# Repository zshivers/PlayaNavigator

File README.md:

# Install dependencies
- `brew install npm websocat`
- `cd test/interactive_map; npm install`
- `cd generated; npm install`

# Running Interactive Map Test
1. Compile for `host` target.
2. `npm start` - Starts the webserver with the map.
3. Go to http://localhost:5173
4. Run the host version, and pipe the websocket data into it - `websocat -s 9998 | ./.pio/build/host/program`

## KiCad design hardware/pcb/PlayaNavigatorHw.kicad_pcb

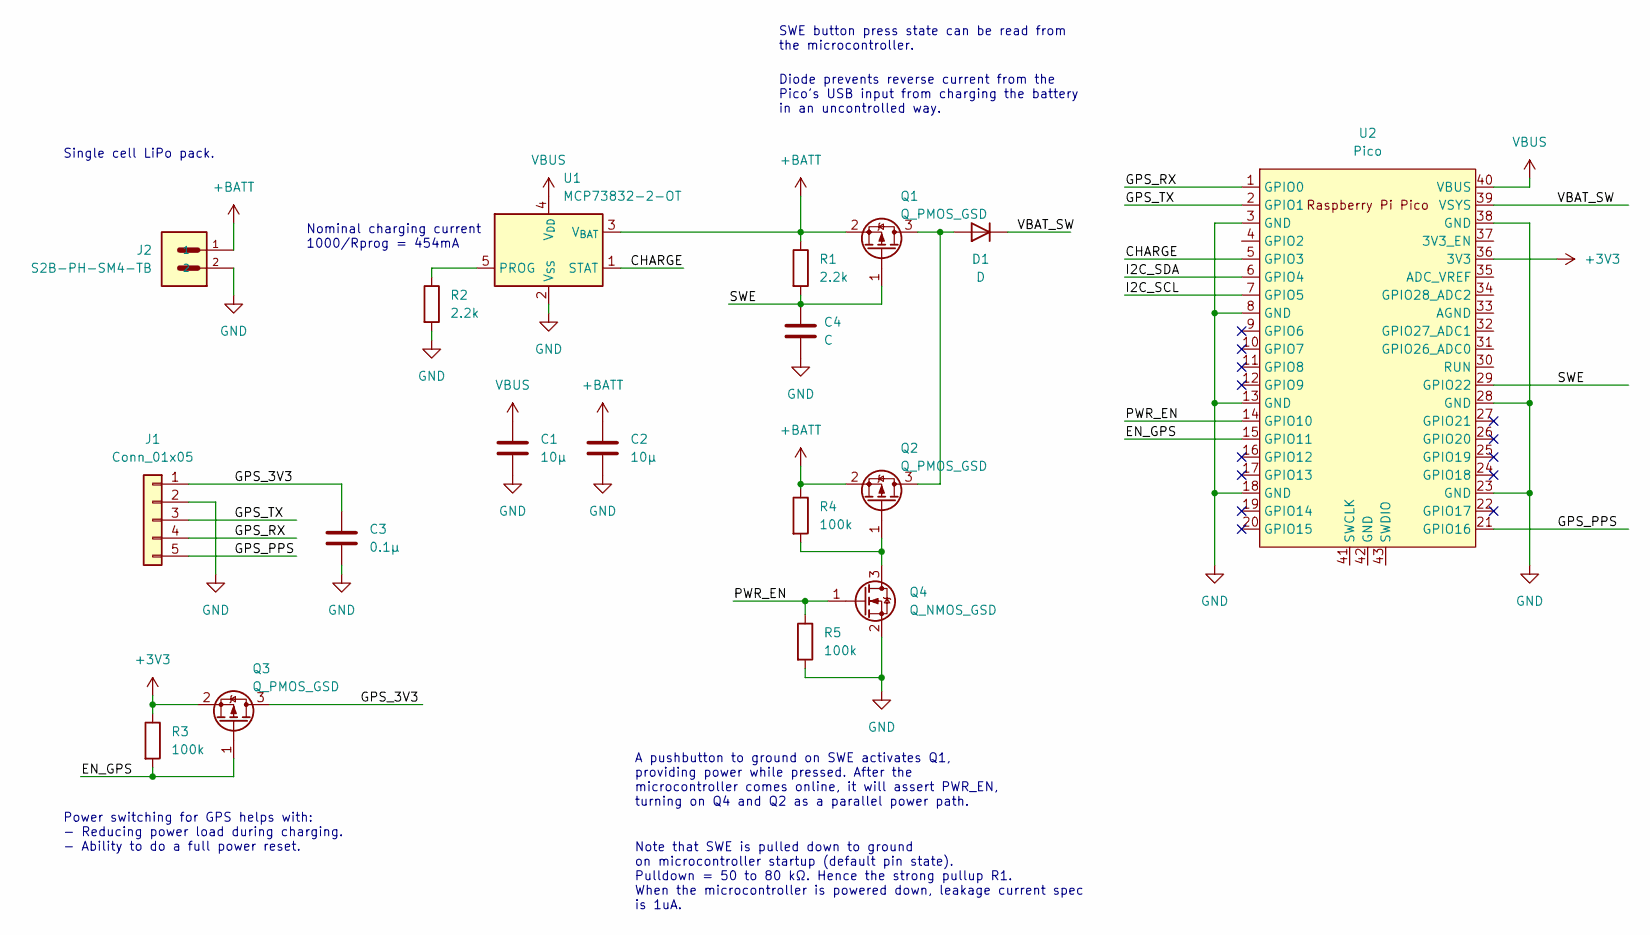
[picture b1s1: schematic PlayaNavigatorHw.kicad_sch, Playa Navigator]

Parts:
C1, C2: 10µ; C_1206_3216Metric
C3: 0.1µ; C_0805_2012Metric
C4: C; C_0805_2012Metric
D1: D; Nexperia_CFP3_SOD-123W
J1: Conn_01x05; PinHeader_1x05_P2.54mm_Vertical
J2: S2B-PH-SM4-TB; JST_S2B-PH-SM4-TB
Q1, Q2, Q3: Q_PMOS_GSD; SOT-23-3
Q4: Q_NMOS_GSD; SOT-23-3
R1, R2: 2.2k; C_0603_1608Metric
R3, R4, R5: 100k; C_0603_1608Metric
U1: MCP73832-2-OT; SOT-23-5; Digikey Part Number MCP73832-2ACI/MC-ND
U2: Pico; RPi_Pico_SMD_TH_Customized

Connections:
+3V3: Q3.2 (S), R3.1, U2.36 (3V3)
+BATT: C2.1, J2.1, Q1.2 (S), Q2.2 (S), R1.1, R4.1, U1.3 (V_{BAT})
/CHARGE: U1.1 (STAT), U2.5 (GPIO3)
/EN_GPS: Q3.1 (G), R3.2, U2.15 (GPIO11)
/GPS_3V3: C3.1, J1.1, Q3.3 (D)
/GPS_PPS: J1.5, U2.21 (GPIO16)
/GPS_RX: J1.4, U2.1 (GPIO0)
/GPS_TX: J1.3, U2.2 (GPIO1)
/I2C_SCL: U2.7 (GPIO5)
/I2C_SDA: U2.6 (GPIO4)
/PWR_EN: Q4.1 (G), R5.1, U2.14 (GPIO10)
/SWE: C4.1, Q1.1 (G), R1.2, U2.29 (GPIO22)
/VBAT_SW: D1.1 (K), U2.39 (VSYS)
GND: C1.2, C2.2, C3.2, C4.2, J1.2, J2.2, Q4.2 (S), R2.2, R5.2, U1.2 (V_{SS}), U2.3 (GND), U2.8 (GND), U2.13 (GND), U2.18 (GND), U2.23 (GND), U2.28 (GND), U2.38 (GND)
unnamed: D1.2 (A), Q1.3 (D), Q2.3 (D)
unnamed: Q2.1 (G), Q4.3 (D), R4.2
unnamed: R2.1, U1.5 (PROG)
VBUS: C1.1, U1.4 (V_{DD}), U2.40 (VBUS)

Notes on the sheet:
Diode prevents reverse current from the Pico's USB input from charging the battery in an uncontrolled way.
Note that SWE is pulled down to ground on microcontroller startup (default pin state). Pulldown = 50 to 80 kΩ. Hence the strong pullup R1. When the microcontroller is powered down, leakage current spec is 1uA.
Nominal charging current 1000/Rprog = 454mA
A pushbutton to ground on SWE activates Q1, providing power while pressed. After the microcontroller comes online, it will assert PWR_EN, turning on Q4 and Q2 as a parallel power path.
Power switching for GPS helps with: - Reducing power load during charging. - Ability to do a full power reset.
Single cell LiPo pack.
SWE button press state can be read from the microcontroller.

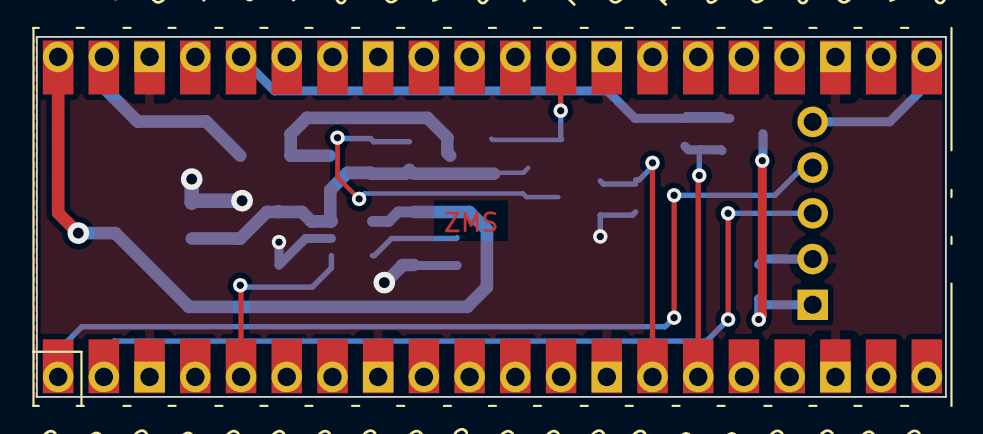
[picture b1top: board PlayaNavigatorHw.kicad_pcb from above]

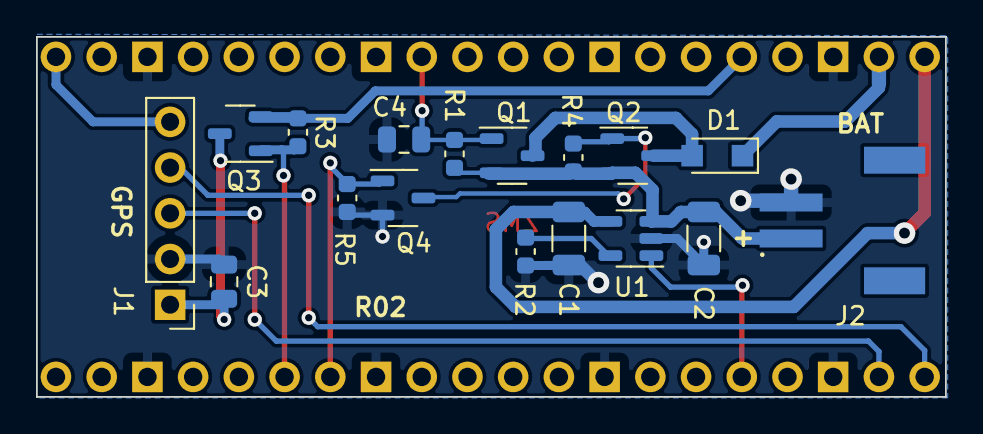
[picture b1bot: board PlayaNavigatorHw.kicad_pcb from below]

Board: 2 copper layers, 50.5 x 20.0 mm, 18 parts (17 on the bottom side), 16 nets.

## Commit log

2023-05-09 Added coordinate library for converting lat/lon to playa map relative coordinates.
2023-05-23 - Build targets for pico and native - Adapted driver for ST7567 - Abstraction for UI
2023-05-29 Mostly functional!
2023-07-13 Idk, lots of improvements.
2023-07-16 Fixed issues with coordinates library, more work on automatic shutdown.
2023-07-27 Bug fix for PPS input, removed button class, updated playa config with coordinates released for 2023.
2023-07-29 Implemented auto-shutdown
2023-07-30 Added temperature measurement
2023-07-30 Add temperature sensing
2023-07-30 Fixed rounding error in clock address and added test
2023-07-30 Document auto shutdown
2023-08-01 Actually improve direction finding.
2023-08-12 Various improvements - Script to generate bathroom lat/lon from the BMorg published data. - Better shutdown move detection logic that does not rely on the GPS speed estimate. - Host GPS class now tak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
2023-08-14 Revert host GPS to using keyboard input.
2023-08-14 Add a spinning burning man animation.
    The animation is activated when near the man's location.
2023-08-14 Improve the interactive map test.
    Now uses real burning man released data!
2023-08-17 Add splash screen.
2023-08-19 Add USB storage and reading map/bathrooms from JSON file.
2023-08-19 Remote unique_ptr in UI class.
2023-08-21 Minor cleanups
2023-08-21 Fix issue with USB storage on first upload. Remove some unnecessary files.
2023-08-24 Added a real README
2023-08-24 Use the watchdog timer.
2023-08-24 Update map_config.json
    Add "-USB" to name to differentiate it from the default 2023 config name.
2023-11-02 Fomatting changes, remove empty auto shutdown test.
2023-11-02 New directory structure to include hardware files
2023-11-02 Remove lib_test targets
2023-11-18 Add firmware for testing hardware.
2023-11-18 Move toilet location script into script/
2023-11-18 Add PCB design files
2023-11-18 Move README into interactive_map/
2023-11-18 Add Fusion360 files
2023-11-18 Pass around Backlight ref instead of pointer.
2023-11-18 Factor out conversion functions into a new header.
2024-02-02 Create LICENSE
